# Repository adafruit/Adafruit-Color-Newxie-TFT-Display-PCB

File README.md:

## Adafruit 1.14 240x135 Color Newxie TFT Display - ST7789 PCB

<a href="http://www.adafruit.com/products/6113"><br/>
Click here to purchase one from the Adafruit shop</a>

PCB files for the Adafruit 1.14 240x135 Color Newxie TFT Display - ST7789. 

Format is EagleCAD schematic and board layout
* https://www.adafruit.com/product/6113

### Description

Say hello to our new Newxie 1.14" 240x135 Color TFT Display Boards – we think it's T-F-Terrific! It's the size of your thumbnail, with glorious 240x135 high res pixel color. This very very small display is only 1.14" diagonal, packed with RGB pixels, for making very small high-density displays. And this breakout board is designed for compact 'stacking' on a 0.1" grid - with a vertical arrangement that mimics old-school nixie tubes. 

The display uses plain SPI (Clock, Data In, Chip Select, Data/Command) to communicate and has its own pixel-addressable frame buffer, it can be used with every kind of microcontroller. Even a very small one with low memory and few pins available! The 1.14" display has 240x135 16-bit full color pixels and is an IPS display, so the color looks great up to 80 degrees off axis in any direction. The TFT driver (ST7789) is very similar to the popular ST7735, and our Arduino library supports it well.

It's essentially the same display & breakout as our 1.14" TFT breakout but minimized: we don't include a MicroSD card or reset line. That means we have only 7 pins required to control the display and backlight. Since the display itself is 0.8" wide, it makes for a perfect fit. We pre-soldered on 2x7 right-angle headers to make it easy to design a stand-up display, both rows are the same contact - we just use dual row for better mechanical stability and so its easier to get them nice and straight. 

Our breakout has the TFT display pre-attached, as well as a ultra-low-dropout 3.3V regulator and a 3/5V level shifter so you can use it with 3.3V or 5V power and logic such as Arduino compatible, ESP32, RP2040 or Raspberry Pi computer.

Of course, we wouldn't just leave you with a datasheet and a "good luck!" - we've written a full open source graphics library that can draw pixels, lines, rectangles, circles, text and bitmaps as well as example code and a wiring tutorial, we also have CircuitPython/Python support for the 1.14" TFT with ST7789.

### License

Adafruit invests time and resources providing this open source design, please support Adafruit and open-source hardware by purchasing products from [Adafruit](https://www.adafruit.com)!

Designed by Limor Fried/Ladyada for Adafruit Industries.

Creative Commons Attribution/Share-Alike, all text above must be included in any redistribution. 
See license.txt for additional details.

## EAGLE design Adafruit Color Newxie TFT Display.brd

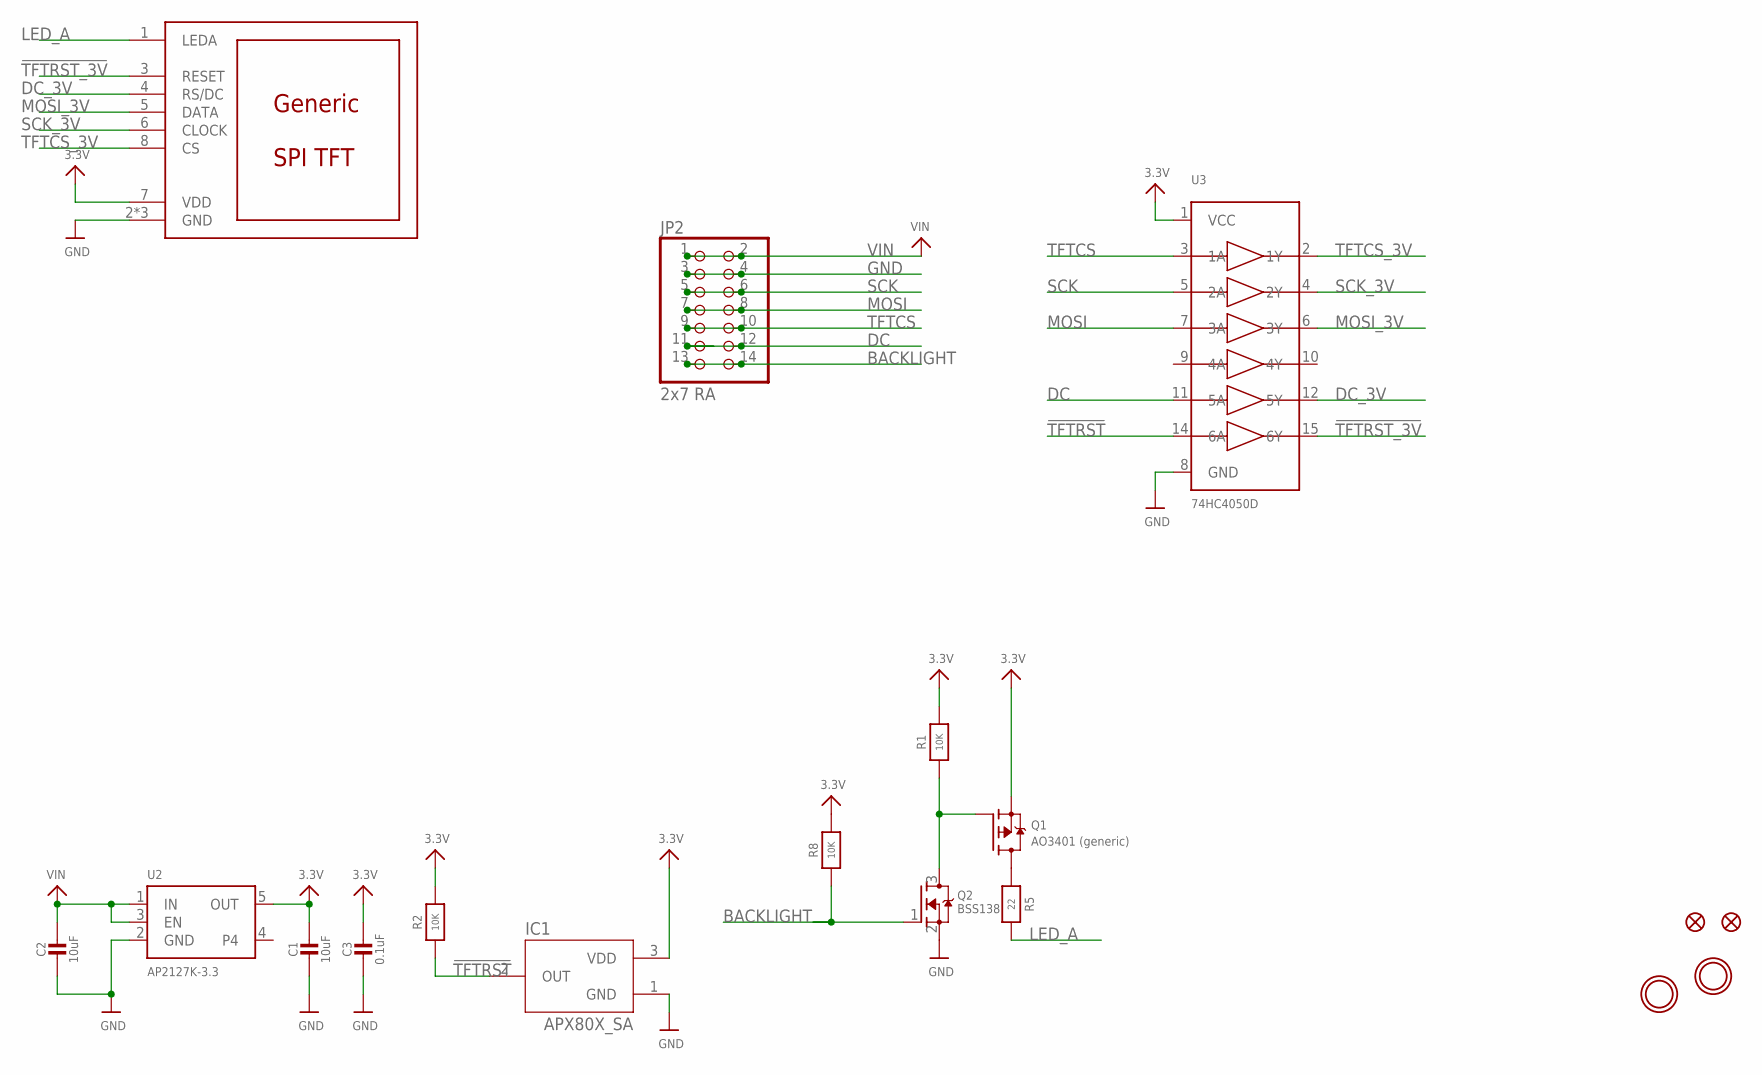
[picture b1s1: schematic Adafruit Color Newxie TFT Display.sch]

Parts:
C1, C2: 10uF; 0805-NO
C3: 0.1uF; 0603-NO
DISP2: DISP_LCD_GENERIC_SPI_NOLEDA_1.14_240X135_FPC; TFT_1.14IN_240X135_FPC
FID1, FID2: FIDUCIAL_1MM
IC1: APX80X_SA; SOT23-WIDE
JP2: 2x7 RA; 2X07_ROUND_70MIL
Q1: AO3401 (generic); SOT23-WIDE
Q2: BSS138; SOT23-WIDE
R1, R2, R8: 10K; 0603-NO
R5: 22; 0603-NO
U2: AP2127K-3.3; SOT23-5
U3: 74HC4050D; TSSOP16
U$9, U$10: MOUNTINGHOLE2.5; MOUNTINGHOLE_2.5_PLATED

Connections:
3.3V: C1.1, C3.1, DISP2.7 (VDD), IC1.3 (VDD), Q1.2 (S), R1.2, R2.2, R8.2, U2.5 (OUT), U3.1 (VCC)
!TFTRST: IC1.2 (OUT), R2.1, U3.14 (6A)
!TFTRST_3V: DISP2.3 (RESET), U3.15 (6Y)
BACKLIGHT: JP2.13, JP2.14, Q2.1 (G), R8.1
DC: JP2.11, JP2.12, U3.11 (5A)
DC_3V: DISP2.4 (RS/DC), U3.12 (5Y)
GND: C1.2, C2.2, C3.2, DISP2.2 (GND), DISP2.MT1 (GND), DISP2.MT2 (GND), IC1.1 (GND), JP2.3, JP2.4, Q2.2 (S), U2.2 (GND), U3.8 (GND)
LED_A: DISP2.1 (LEDA), R5.2
MOSI: JP2.7, JP2.8, U3.7 (3A)
MOSI_3V: DISP2.5 (DATA), U3.6 (3Y)
unnamed: Q1.3 (D), R5.1
unnamed: Q1.1 (G), Q2.3 (D), R1.1
SCK: JP2.5, JP2.6, U3.5 (2A)
SCK_3V: DISP2.6 (CLOCK), U3.4 (2Y)
TFTCS: JP2.9, JP2.10, U3.3 (1A)
TFTCS_3V: DISP2.8 (CS), U3.2 (1Y)
VIN: C2.1, JP2.1, JP2.2, U2.1 (IN), U2.3 (EN)

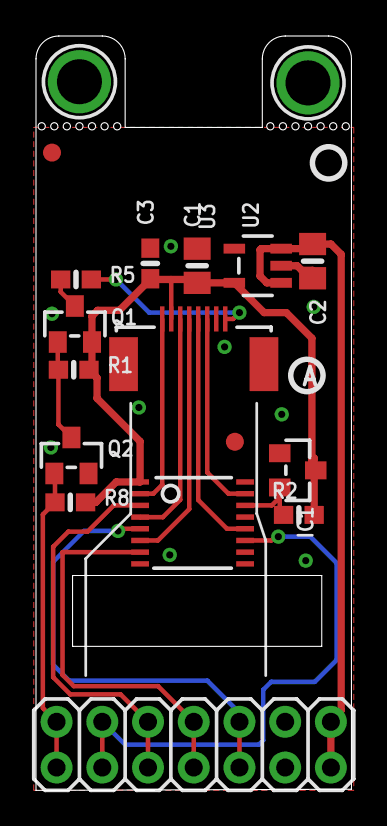
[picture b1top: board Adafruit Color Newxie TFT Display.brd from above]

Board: 2 copper layers, 17.5 x 41.9 mm, 28 parts (1 on the bottom side), 17 nets.

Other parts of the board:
PLABEL0: PLABEL0
PLABEL1: PLABEL1
PLABEL2: PLABEL2
PLABEL3: PLABEL3
PLABEL4: PLABEL4
PLABEL5: PLABEL5
PLABEL6: PLABEL6
PLABEL7: PLABEL7
U$6, U$15: PCBFEAT-REV-040

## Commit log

2024-12-18 cookiecutter
